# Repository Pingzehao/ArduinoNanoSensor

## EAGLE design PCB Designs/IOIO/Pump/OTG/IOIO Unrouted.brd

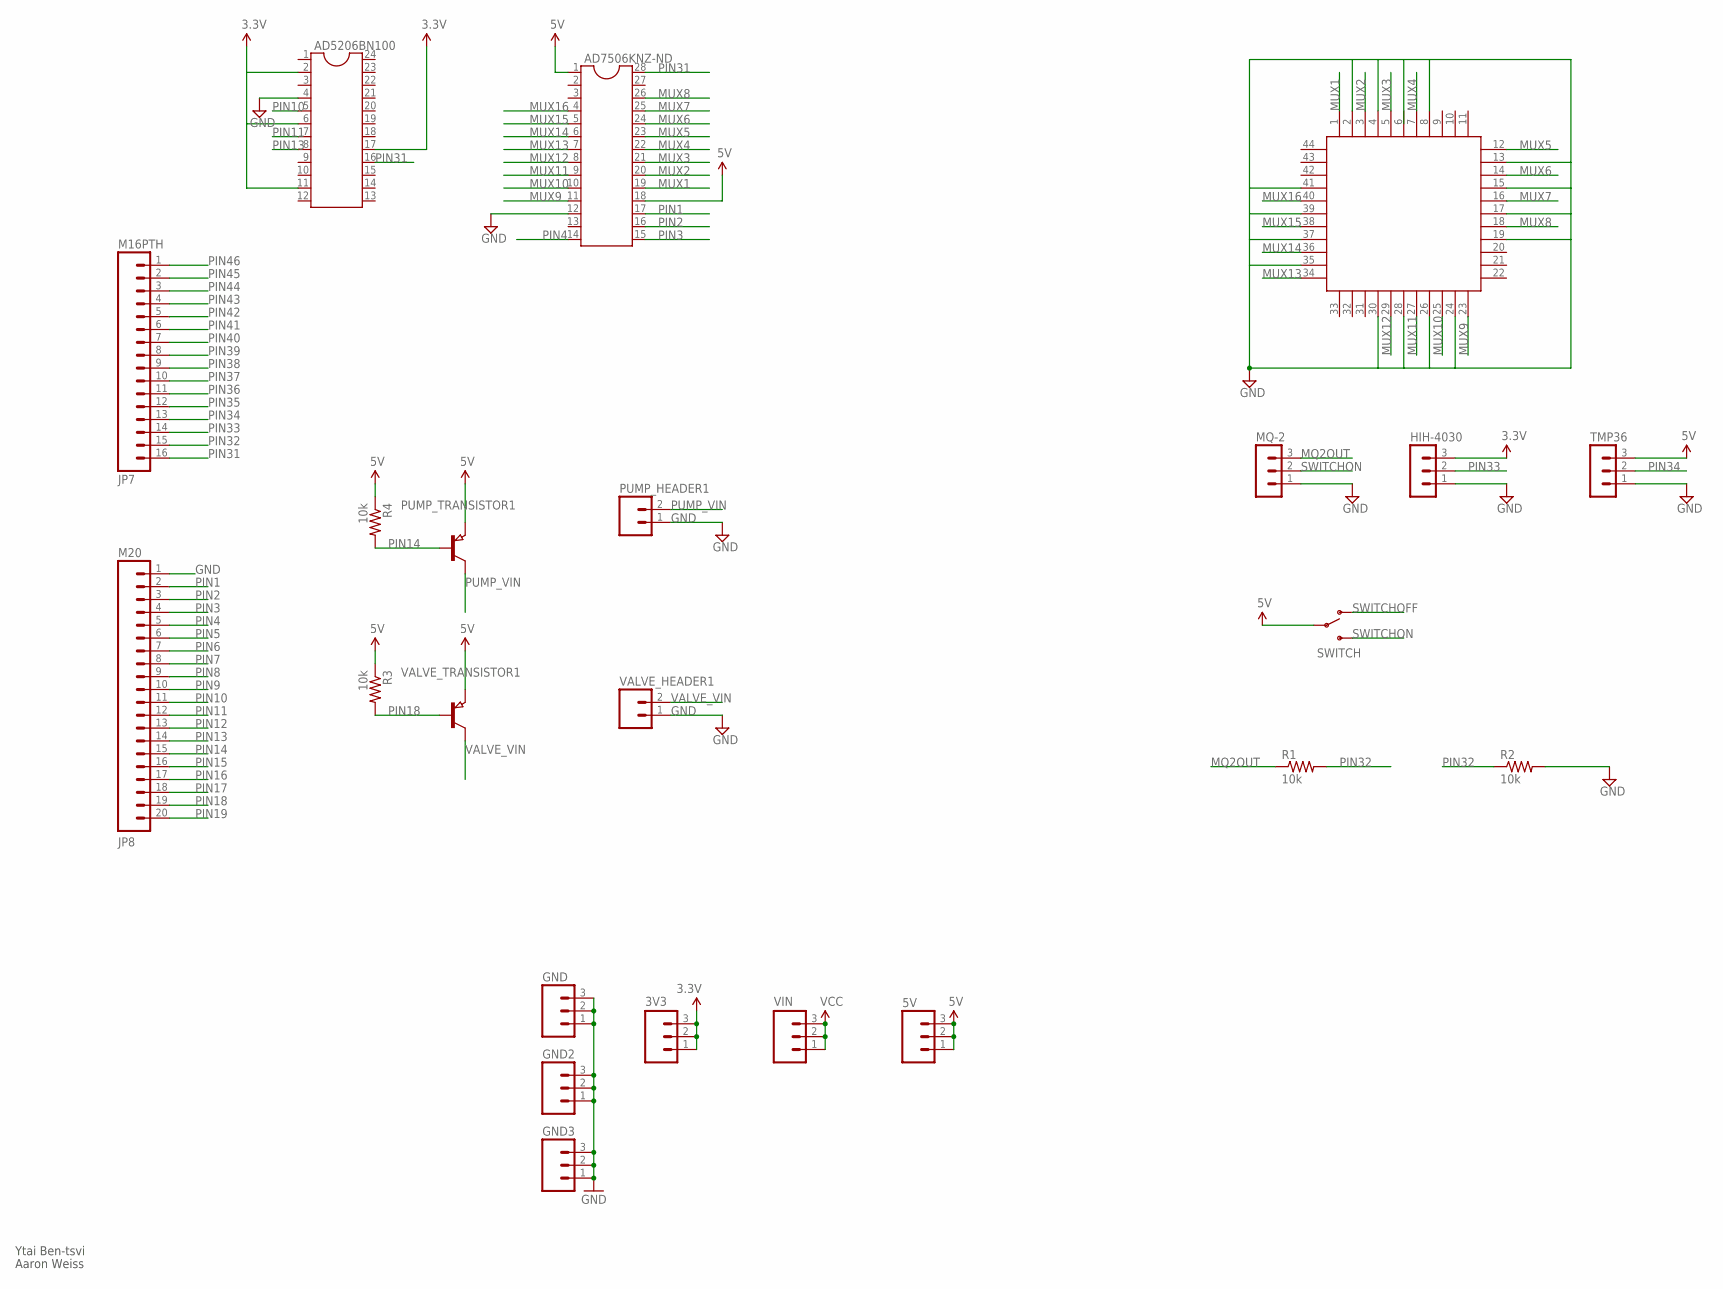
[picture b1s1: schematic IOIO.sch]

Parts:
3V3, 5V: M03PTH; 1X03
AD5206BN100: DIL24-3
AD7506KNZ-ND: DIL28; DIL28-6
GND, GND2, GND3: M03PTH; 1X03
HIH-4030: MA03-1
JP7: M16PTH; 1X16
JP8: M20; 1X20
MQ-2: MA03-1
PUMP_HEADER1: M02PTH; 1X02
PUMP_TRANSISTOR1: PNP-TRANSISTOR_SOT23; SOT23
R1, R2: 10k; 0207/7
R3, R4: 10k; M2012
SWITCH: SWITCH-SPSTPTH; SWITCH-SPDT
TMP36: MA03-1
U$1: S44
VALVE_HEADER1: M02PTH; 1X02
VALVE_TRANSISTOR1: PNP-TRANSISTOR_SOT23; SOT23
VIN: M03PTH; 1X03

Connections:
3.3V: 3V3.1, 3V3.2, 3V3.3, AD5206BN100.2, AD5206BN100.6, AD5206BN100.11, AD5206BN100.17, HIH-4030.3
5V: 5V.1, 5V.2, 5V.3, AD7506KNZ-ND.1, AD7506KNZ-ND.18, PUMP_TRANSISTOR1.2 (E), R3.1, R4.1, SWITCH.2, TMP36.3, VALVE_TRANSISTOR1.2 (E)
GND: AD5206BN100.4, AD7506KNZ-ND.12, GND.1, GND.2, GND.3, GND2.1, GND2.2, GND2.3, GND3.1, GND3.2, GND3.3, HIH-4030.1, JP8.1, MQ-2.1, PUMP_HEADER1.1, R2.2, TMP36.1, U$1.2, U$1.4, U$1.8, U$1.13, U$1.15, U$1.17, U$1.19, U$1.24, U$1.26, U$1.28, U$1.30, U$1.35, U$1.37, U$1.39, U$1.41, VALVE_HEADER1.1
MQ2OUT: MQ-2.3, R1.1
MUX1: AD7506KNZ-ND.19, U$1.1
MUX2: AD7506KNZ-ND.20, U$1.3
MUX3: AD7506KNZ-ND.21, U$1.5
MUX4: AD7506KNZ-ND.22, U$1.7
MUX5: AD7506KNZ-ND.23, U$1.12
MUX6: AD7506KNZ-ND.24, U$1.14
MUX7: AD7506KNZ-ND.25, U$1.16
MUX8: AD7506KNZ-ND.26, U$1.18
MUX9: AD7506KNZ-ND.11, U$1.23
MUX10: AD7506KNZ-ND.10, U$1.25
MUX11: AD7506KNZ-ND.9, U$1.27
MUX12: AD7506KNZ-ND.8, U$1.29
MUX13: AD7506KNZ-ND.7, U$1.34
MUX14: AD7506KNZ-ND.6, U$1.36
MUX15: AD7506KNZ-ND.5, U$1.38
MUX16: AD7506KNZ-ND.4, U$1.40
PIN1: AD7506KNZ-ND.17, JP8.2
PIN2: AD7506KNZ-ND.16, JP8.3
PIN3: AD7506KNZ-ND.15, JP8.4
PIN4: AD7506KNZ-ND.14, JP8.5
PIN5: JP8.6
PIN6: JP8.7
PIN7: JP8.8
PIN8: JP8.9
PIN9: JP8.10
PIN10: AD5206BN100.5, JP8.11
PIN11: AD5206BN100.7, JP8.12
PIN12: JP8.13
PIN13: AD5206BN100.8, JP8.14
PIN14: JP8.15, PUMP_TRANSISTOR1.1 (B), R4.2
PIN15: JP8.16
PIN16: JP8.17
PIN17: JP8.18
PIN18: JP8.19, R3.2, VALVE_TRANSISTOR1.1 (B)
PIN19: JP8.20
PIN31: AD5206BN100.16, AD7506KNZ-ND.28, JP7.16
PIN32: JP7.15, R1.2, R2.1
PIN33: HIH-4030.2, JP7.14
PIN34: JP7.13, TMP36.2
PIN35: JP7.12
PIN36: JP7.11
PIN37: JP7.10
PIN38: JP7.9
PIN39: JP7.8
PIN40: JP7.7
PIN41: JP7.6
PIN42: JP7.5
PIN43: JP7.4
PIN44: JP7.3
PIN45: JP7.2
PIN46: JP7.1
PUMP_VIN: PUMP_HEADER1.2, PUMP_TRANSISTOR1.3 (C)
SWITCHOFF: SWITCH.1 (O)
SWITCHON: MQ-2.2, SWITCH.3 (S)
VALVE_VIN: VALVE_HEADER1.2, VALVE_TRANSISTOR1.3 (C)
VCC: VIN.1, VIN.2, VIN.3

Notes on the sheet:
Ytai Ben-tsvi
Aaron Weiss

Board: 2 copper layers, 23 parts (0 on the bottom side), 37 nets, no tracks yet.

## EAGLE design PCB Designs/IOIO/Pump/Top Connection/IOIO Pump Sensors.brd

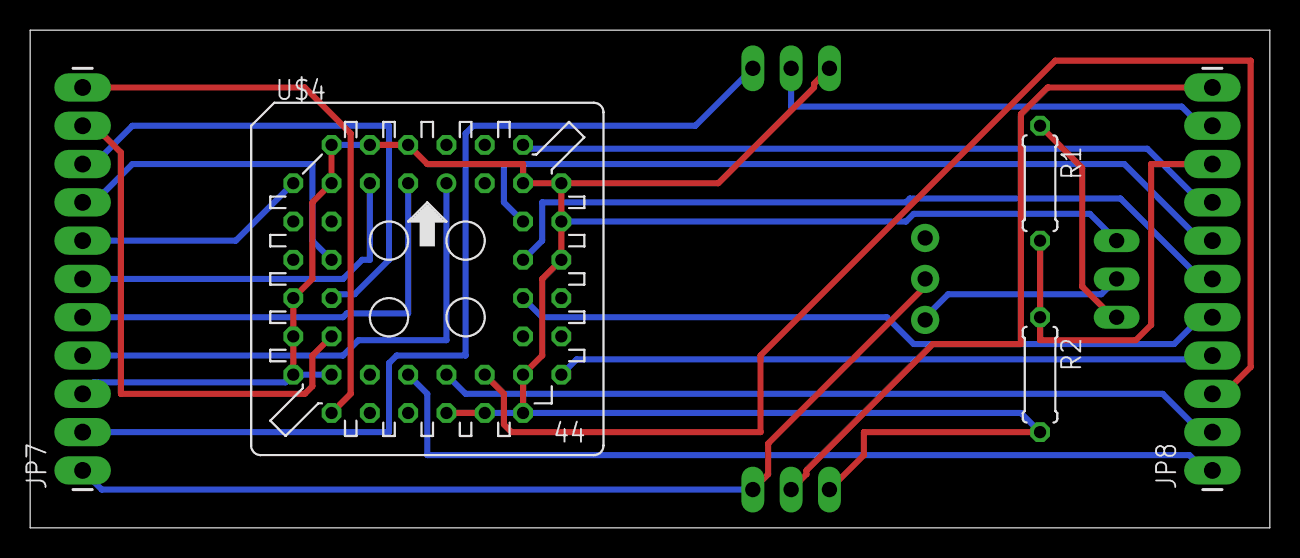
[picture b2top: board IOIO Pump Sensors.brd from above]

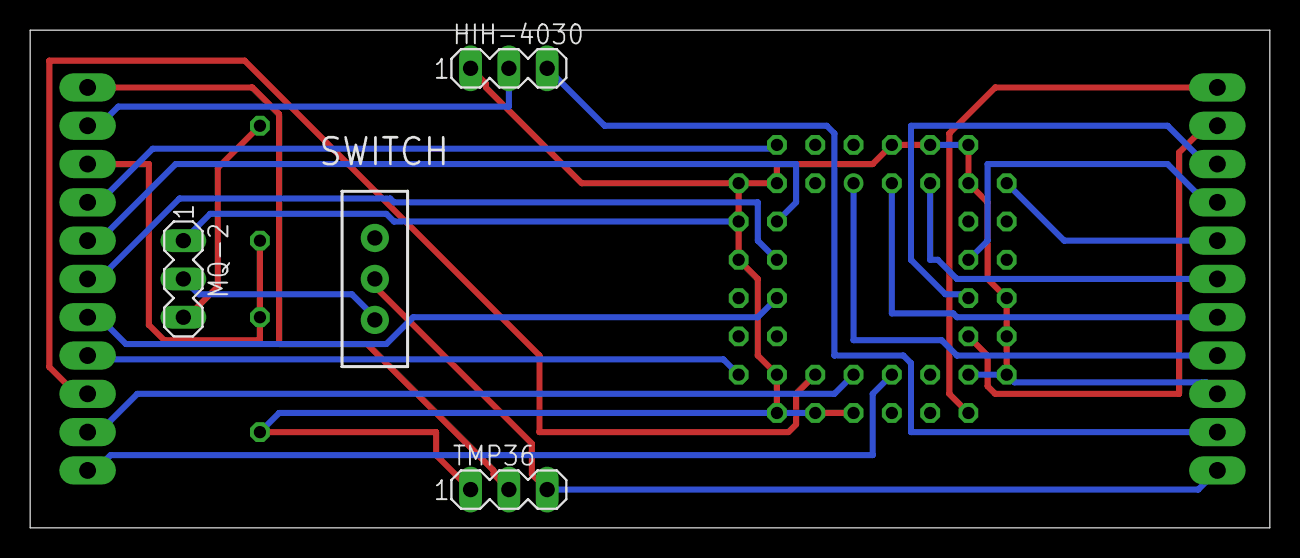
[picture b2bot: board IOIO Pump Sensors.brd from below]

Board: 2 copper layers, 82.2 x 33.0 mm, 9 parts (4 on the bottom side), 24 nets.

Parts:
HIH-4030: MA03-1
JP7, JP8: M11LONGPADS; 1X11_LONGPADS
MQ-2: MA03-1
R1, R2: 10k; 0207/7
SWITCH: SWITCH-SPDT_LOCK.007S
TMP36: MA03-1
U$4: S44

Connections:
3.3V: HIH-4030.3, JP7.2
5V: JP7.1, SWITCH.2, TMP36.3
GND: HIH-4030.1, JP7.3, MQ-2.1, R2.2, TMP36.1, U$4.2, U$4.4, U$4.6, U$4.8, U$4.13, U$4.15, U$4.17, U$4.19, U$4.24, U$4.26, U$4.28, U$4.30, U$4.35, U$4.37, U$4.39, U$4.41
MQ2OUT: MQ-2.3, R1.1
MUX1: JP7.4, U$4.1
MUX2: JP7.5, U$4.3
MUX3: JP7.6, U$4.5
MUX4: JP7.7, U$4.7
MUX5: JP7.8, U$4.12
MUX6: JP7.9, U$4.14
MUX7: JP7.10, U$4.16
MUX8: JP7.11, U$4.18
MUX9: JP8.1, U$4.23
MUX10: JP8.2, U$4.25
MUX11: JP8.3, U$4.27
MUX12: JP8.4, U$4.29
MUX13: JP8.5, U$4.34
MUX14: JP8.6, U$4.36
MUX15: JP8.7, U$4.38
MUX16: JP8.8, U$4.40
PIN32: JP8.9, R1.2, R2.1
PIN33: HIH-4030.2, JP8.10
PIN34: JP8.11, TMP36.2
SWITCHON: MQ-2.2, SWITCH.3

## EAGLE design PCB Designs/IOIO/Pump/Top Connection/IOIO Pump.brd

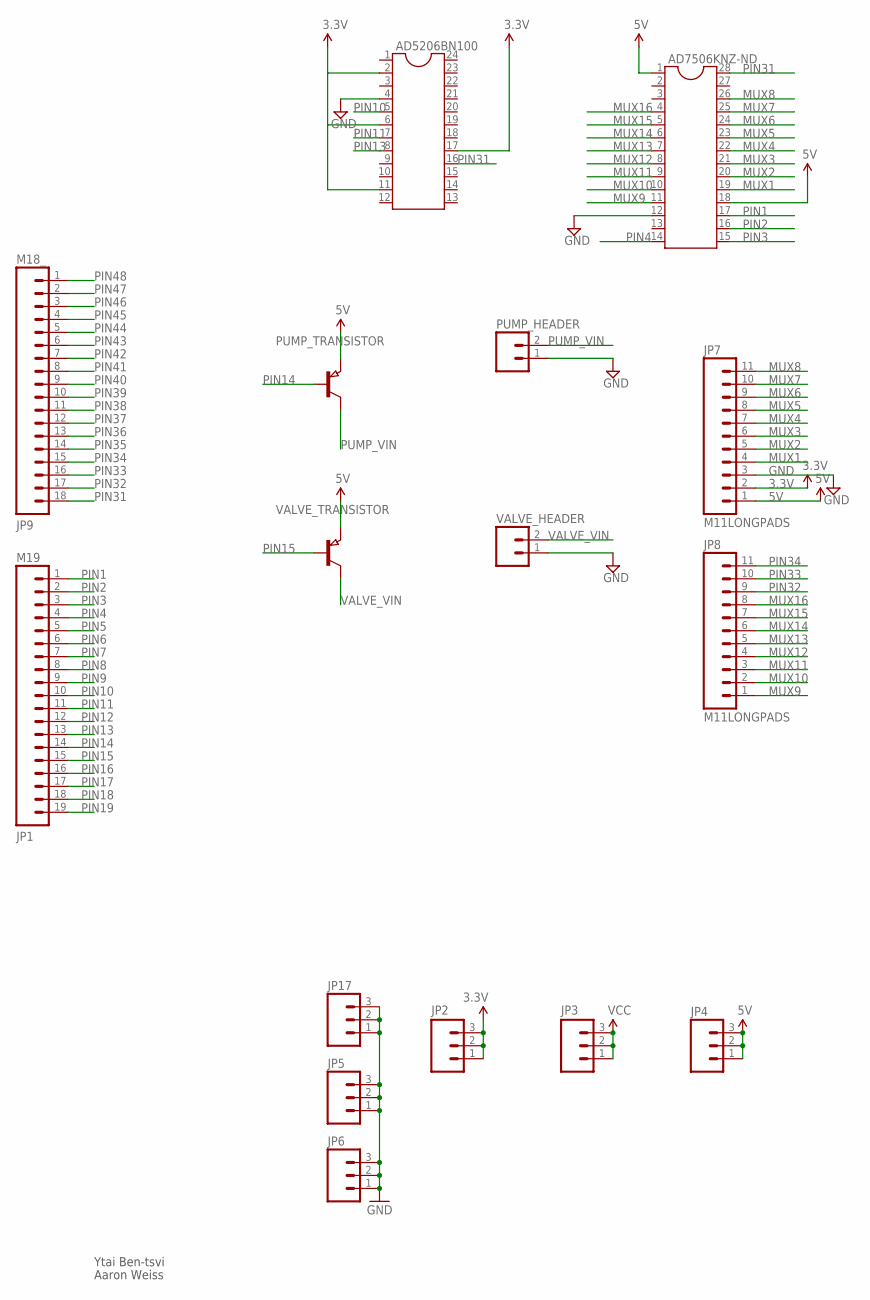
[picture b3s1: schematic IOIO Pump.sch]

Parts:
AD5206BN100: DIL24-3
AD7506KNZ-ND: DIL28; DIL28-6
JP1: M19; 1X19
JP2, JP3, JP4, JP5, JP6, JP17: M03PTH; 1X03
JP7, JP8: M11LONGPADS; 1X11_LONGPADS
JP9: M18_; 1X18
PUMP_HEADER: M02PTH; 1X02
PUMP_TRANSISTOR: PNP-TRANSISTOR_SOT23; SOT23
VALVE_HEADER: M02PTH; 1X02
VALVE_TRANSISTOR: PNP-TRANSISTOR_SOT23; SOT23

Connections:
3.3V: AD5206BN100.2, AD5206BN100.6, AD5206BN100.11, AD5206BN100.17, JP2.1, JP2.2, JP2.3, JP7.2
5V: AD7506KNZ-ND.1, AD7506KNZ-ND.18, JP4.1, JP4.2, JP4.3, JP7.1, PUMP_TRANSISTOR.2 (E), VALVE_TRANSISTOR.2 (E)
GND: AD5206BN100.4, AD7506KNZ-ND.12, JP5.1, JP5.2, JP5.3, JP6.1, JP6.2, JP6.3, JP7.3, JP17.1, JP17.2, JP17.3, PUMP_HEADER.1, VALVE_HEADER.1
MUX1: AD7506KNZ-ND.19, JP7.4
MUX2: AD7506KNZ-ND.20, JP7.5
MUX3: AD7506KNZ-ND.21, JP7.6
MUX4: AD7506KNZ-ND.22, JP7.7
MUX5: AD7506KNZ-ND.23, JP7.8
MUX6: AD7506KNZ-ND.24, JP7.9
MUX7: AD7506KNZ-ND.25, JP7.10
MUX8: AD7506KNZ-ND.26, JP7.11
MUX9: AD7506KNZ-ND.11, JP8.1
MUX10: AD7506KNZ-ND.10, JP8.2
MUX11: AD7506KNZ-ND.9, JP8.3
MUX12: AD7506KNZ-ND.8, JP8.4
MUX13: AD7506KNZ-ND.7, JP8.5
MUX14: AD7506KNZ-ND.6, JP8.6
MUX15: AD7506KNZ-ND.5, JP8.7
MUX16: AD7506KNZ-ND.4, JP8.8
PIN1: AD7506KNZ-ND.17, JP1.1
PIN2: AD7506KNZ-ND.16, JP1.2
PIN3: AD7506KNZ-ND.15, JP1.3
PIN4: AD7506KNZ-ND.14, JP1.4
PIN5: JP1.5
PIN6: JP1.6
PIN7: JP1.7
PIN8: JP1.8
PIN9: JP1.9
PIN10: AD5206BN100.5, JP1.10
PIN11: AD5206BN100.7, JP1.11
PIN12: JP1.12
PIN13: AD5206BN100.8, JP1.13
PIN14: JP1.14, PUMP_TRANSISTOR.1 (B)
PIN15: JP1.15, VALVE_TRANSISTOR.1 (B)
PIN16: JP1.16
PIN17: JP1.17
PIN18: JP1.18
PIN19: JP1.19
PIN31: AD5206BN100.16, AD7506KNZ-ND.28, JP9.18
PIN32: JP8.9, JP9.17
PIN33: JP8.10, JP9.16
PIN34: JP8.11, JP9.15
PIN35: JP9.14
PIN36: JP9.13
PIN37: JP9.12
PIN38: JP9.11
PIN39: JP9.10
PIN40: JP9.9
PIN41: JP9.8
PIN42: JP9.7
PIN43: JP9.6
PIN44: JP9.5
PIN45: JP9.4
PIN46: JP9.3
PIN47: JP9.2
PIN48: JP9.1
PUMP_VIN: PUMP_HEADER.2, PUMP_TRANSISTOR.3 (C)
VALVE_VIN: VALVE_HEADER.2, VALVE_TRANSISTOR.3 (C)
VCC: JP3.1, JP3.2, JP3.3

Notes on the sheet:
Ytai Ben-tsvi
Aaron Weiss

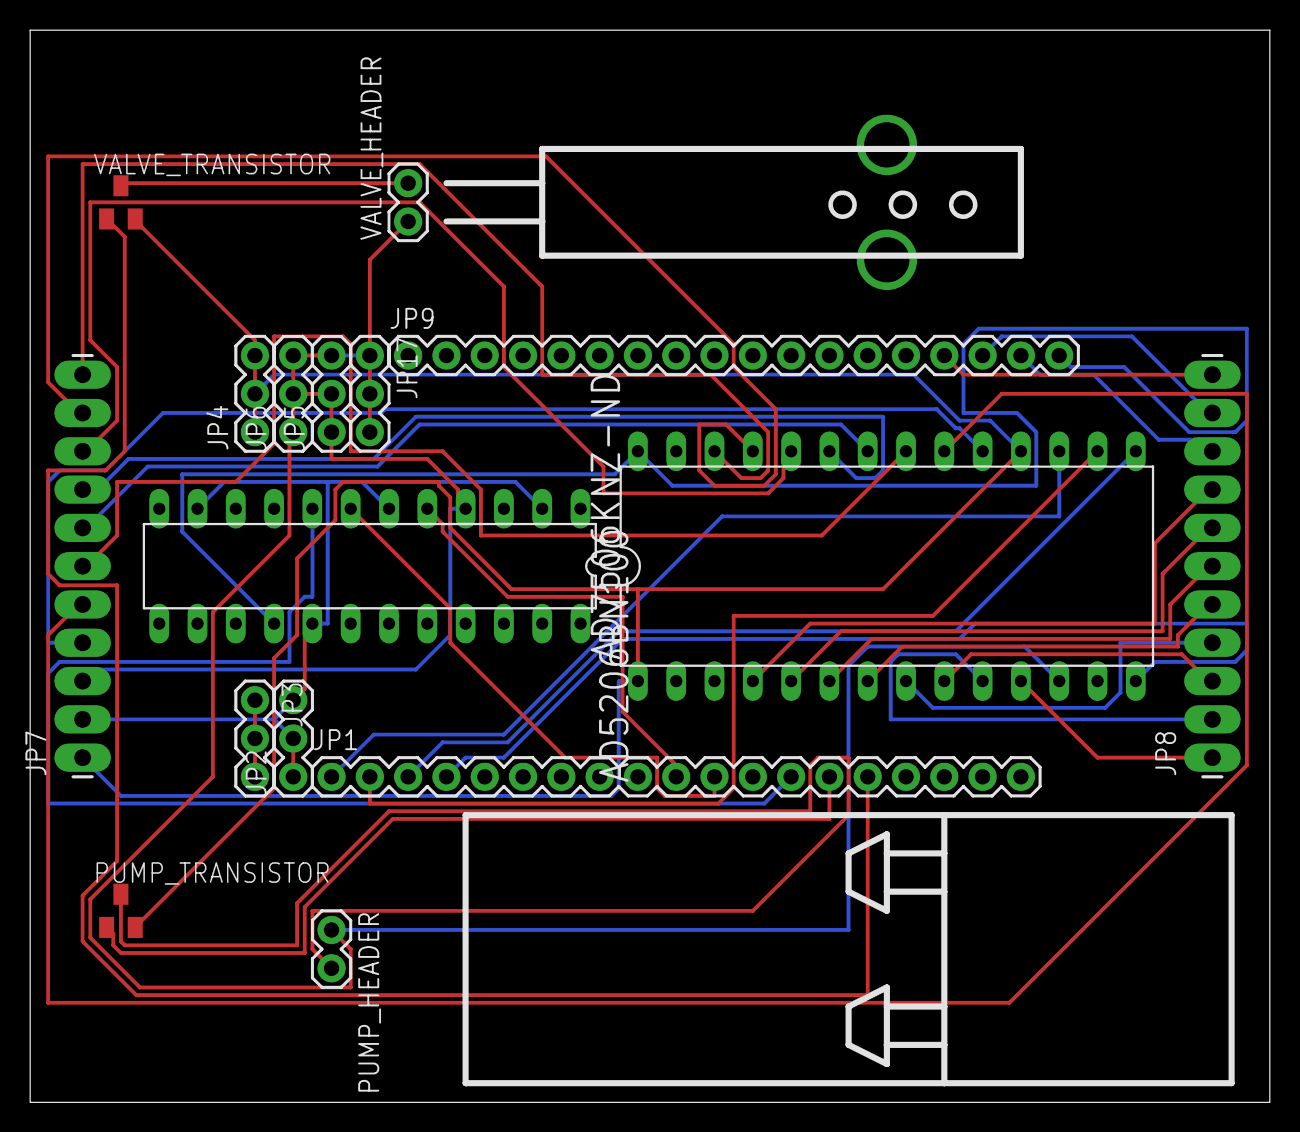
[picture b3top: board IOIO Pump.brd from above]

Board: 2 copper layers, 82.2 x 71.1 mm, 16 parts (0 on the bottom side), 35 nets.

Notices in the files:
parts and their libraries:
SparkFun-Connectors: Licensing: CC v3.0 Share-Alike You are welcome to use this library for commercial purposes.
